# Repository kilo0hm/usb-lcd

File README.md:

# usb-lcd
Connect a HD44780 LCD to USB, via the CH341 IC. This adapter can interface with LCD Smartie, LCDHype, and AIDA64 on Windows. Linux support should be possible too.

See my prototype version working [here](https://www.youtube.com/shorts/TWgQVQCoLs0), and the Rev.A PCB working [here](https://www.youtube.com/watch?v=QafS92o0JMY).

The PCB layout is inspired by the I2C adapter boards commonly found online. It should fit on the back any 16 pin LCD module with a HD44780 (or compatible) driver.

This project was made using the documentation and plugins from ABACOM. You can buy their USB LCD, as well as see all the documentation [here](https://www.electronic-software-shop.com/hardware/usb-lcd-display-4x20-zeichen-gruen.html).

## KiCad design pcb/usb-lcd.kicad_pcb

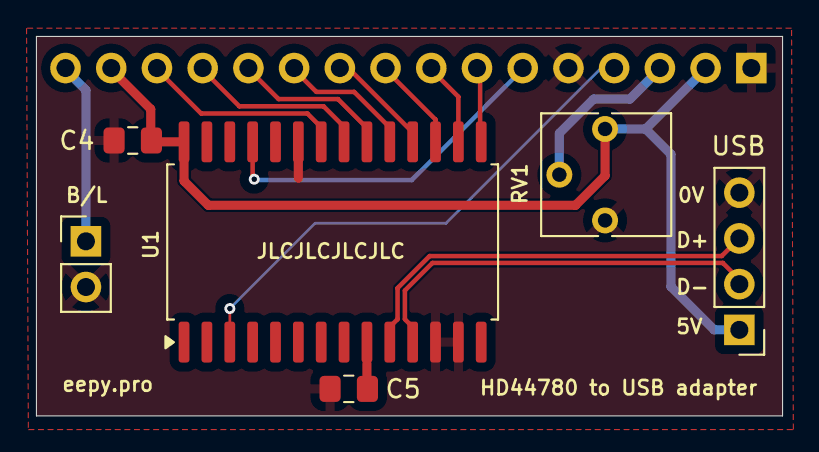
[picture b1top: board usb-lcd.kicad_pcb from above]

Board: 2 copper layers, 41.5 x 21.1 mm, 7 parts (1 on the bottom side), 17 nets.

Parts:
C4: 0.1u; C_0805_2012Metric_Pad1.18x1.45mm_HandSolder
C5: 0.01u; C_0805_2012Metric_Pad1.18x1.45mm_HandSolder
J1: USB; PinHeader_1x04_P2.54mm_Vertical
J2: B/L; PinHeader_1x02_P2.54mm_Vertical
J3: LCD; PinHeader_1x16_P2.54mm_Vertical
RV1: 10K; Potentiometer_Vishay_T73YP_Vertical
U1: CH341B-EPP/MEM; SOP-28_8.4x18.16mm_P1.27mm

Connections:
+5V: C4.1, J1.1, J3.2 (VDD), J3.15 (LED(+)), RV1.1, U1.28 (VCC)
/D+: J1.3, U1.10 (UD+)
/D-: J1.2, U1.11 (UD-)
GND: C4.2, C5.2, J1.4, J2.2, J3.1 (VSS), J3.5 (R/W), RV1.3, U1.12 (GND), U1.13 (X1), U1.23 (SDA)
unnamed: J2.1, J3.16 (LED(-))
unnamed: J3.7 (D0), U1.15 (D0)
unnamed: J3.8 (D1), U1.16 (D1)
unnamed: J3.9 (D2), U1.17 (D2)
unnamed: J3.10 (D3), U1.18 (D3)
unnamed: J3.11 (D4), U1.19 (D4)
unnamed: J3.12 (D5), U1.20 (D5)
unnamed: J3.13 (D6), U1.21 (D6)
unnamed: J3.14 (D7), U1.22 (D7)
unnamed: J3.6 (E), U1.25 (WR#)
unnamed: J3.4 (RS), U1.3 (AS#)
unnamed: J3.3 (VO), RV1.2
unnamed: C5.1, U1.9 (V3)

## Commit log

2025-11-11 Add PCB
2025-11-16 Update PCB
